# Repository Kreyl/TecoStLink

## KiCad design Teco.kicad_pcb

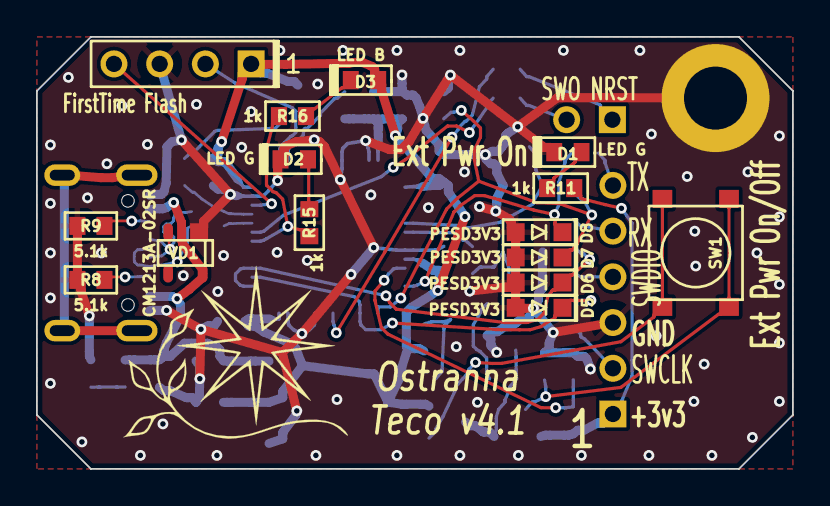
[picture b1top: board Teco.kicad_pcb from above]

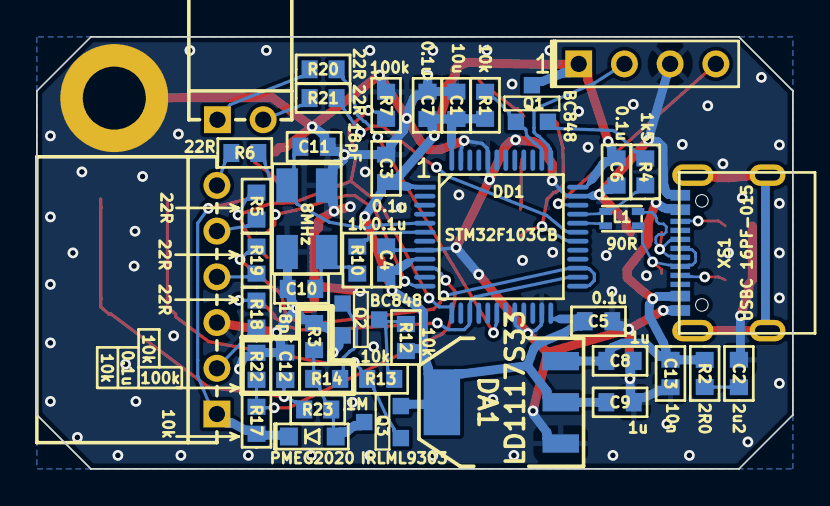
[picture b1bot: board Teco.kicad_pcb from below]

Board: 2 copper layers, 42.0 x 24.0 mm, 59 parts (42 on the bottom side), 40 nets.

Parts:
C1: 10u; CAP_0603
C2: 2u2; CAP_0603
C3, C4, C5, C6, C7, C12: 0.1u; CAP_0603
C8, C9: 1u; CAP_0603
C10, C11: 18pF; CAP_0603
C13: 10n; CAP_0603
D1, D2: LED G; LED_0603
D3: LED B; LED_0603
D4: PMEG2020; SOD323
D5, D6, D7, D8: PESD3V3; SOD323
DA1: LD1117S33; SOT223
DD1: STM32F103CB; LQFP48
HOLE5: HOLE_METALLED; Hole3_5_out6mm
L1: 90R; DLW21SN
Logo1: Logo; Ostranna_12d7_10d1
Q1, Q2: BC848; SOT23-3
Q3: IRLML9303; SOT23-3
R1, R3, R12, R13, R17, R22: 10k; RES_0603
R2: 2R0; RES_0603
R4: 1k5; RES_0603
R5, R6, R18, R19, R20, R21: 22R; RES_0603
R7, R14: 100k; RES_0603
R8, R9: 5.1k; RES0603
R10, R11, R15, R16: 1k; RES_0603
R23: 1M; RES_0603
SW1: BUTTON; BTN_4x4_SMD
VD1: CM1213A−02SR; SOT143
XL2: CONN_4; PLS-4
XL3: CONN_6; PBS-6R-MIRR
XL4: CONN_2; PBS-2R-MIRR
XS1: USBC 16PF-015; USB-C_16pin_16PF-015
XTAL1: 8MHz; 0503x4-4

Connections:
+3v3: C1.1, C3.1, C4.1, C5.1, C6.1, C7.1, C9.1, D3.A, DA1.2 (OUT), DA1.PAD (OUT), DD1.1 (VBAT), DD1.9 (VDDA), DD1.24 (VDD1), DD1.36 (VDD2), DD1.48 (VDD3), Q1.3 (C), Q3.2 (S), R1.2, R12.1, XL2.1
+5v: C8.1, C13.1, DA1.3 (IN), R2.1, VD1.4 (VDD), XS1.A4B9, XS1.B4A9
/AIN1: DD1.10 (ADC1-0/WKUP/PA0), R17.2, R22.1
/EXTPWR: D4.C, R11.2, R17.1, XL3.1
/LED_STLINK: DD1.30 (T1C2/TX1/PA9), R15.2, R16.2
/RXD: D7.C, DD1.13 (ADC1-3/T2C4/T15C2/RX2/PA3), R5.2, R7.1
/STM_JTCK: DD1.37 (SWCLK/JTCK/PA14), XL2.2 (PM)
/STM_JTMS: DD1.34 (SWDIO/JTMS/PA13), XL2.4
/TXD: D8.C, DD1.12 (ADC1-2/T2C3/T15C1/TX2/PA2), R6.2
/T_JTCK: D5.C, DD1.15 (ADC1-5/DAC2/SCK1/PA5), DD1.26 (PB13/SCK2/T1C1N), R18.2
/T_JTMS: D6.C, DD1.25 (PB12/CK3), DD1.27 (PB14/MISO2/T1C2N/(T15C1)), R19.2
/T_NRST: DD1.18 (PB0/T3C3/ADC1-8), R20.2
/T_SWO: DD1.31 (T1C3/RX1/PA10), R21.2
/USB_CC1: R8.2, XS1.A5
/USB_CC2: R9.2, XS1.B5
/USB_D+: DD1.33 (USBDP/PA12), L1.3, R4.1
/USB_D-: DD1.32 (T1C4/USBDM/PA11), L1.2
/USB_DIN+: L1.4, VD1.3 (CH2), XS1.A6, XS1.B6
/USB_DIN-: L1.1, VD1.2 (CH1), XS1.A7, XS1.B7
/USB_RENUM: DD1.38 (JTDI/PA15), Q1.1 (B), R1.1
GND: C1.2, C2.2, C3.2, C4.2, C5.2, C6.2, C7.2, C8.2, C9.2, C10.2, C11.2, C12.2, C13.2, D1.C, D2.C, D5.A, D6.A, D7.A, D8.A, DA1.1 (GND), DD1.8 (VSSA), DD1.20 (PB2/BOOT1), DD1.23 (VSS1), DD1.35 (VSS2), DD1.44 (BOOT0), DD1.47 (VSS3), HOLE5.H, Q2.2 (E), R3.2, R7.2, R8.1, R9.1, R22.2, VD1.1 (GND), XL2.3, XL3.3, XS1.A1B12, XS1.B1A12, XTAL1.H
unnamed: C2.1, R2.2
unnamed: C10.1, R10.1, XTAL1.1
unnamed: C12.1, R23.2, SW1.2
unnamed: D1.A, R11.1
unnamed: D2.A, R15.1
unnamed: D3.C, R16.1
unnamed: C11.1, DD1.5 (OSCIN/(PD0)), XTAL1.2
unnamed: DD1.6 (OSCOUT/(PD1)), R10.2
unnamed: Q1.2 (E), R4.2
unnamed: Q2.1 (B), R14.2
unnamed: Q2.3 (C), R12.2, R13.2
unnamed: D4.A, Q3.3 (D), R3.1, R14.1, R23.1
unnamed: Q3.1 (G), R13.1, SW1.1
unnamed: R5.1, XL3.5
unnamed: R6.1, XL3.6
unnamed: R18.1, XL3.2
unnamed: R19.1, XL3.4
unnamed: R20.1, XL4.1
unnamed: R21.1, XL4.2 (PM)

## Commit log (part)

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2017-04-27 + Sch done, PCB started
2017-04-27 Sch updated Layout done
2017-04-28 Sent to production
2017-05-05 + botloader binaries
2017-05-12 + R to discharge pwr line
2019-04-22 + v3 Sent to factory
2019-04-22 + V2
2019-04-22 v3.1: + Pull-up on RX + legend
2019-11-25 + complete fw
2019-11-25 + STLink upgrade tool v3.7.0. Newer ones do not allow to upgrade it from scratch.
2020-05-28 + Readme + St-Link upgrade
2020-05-29 + Teco v4 + USB renum returned!
2023-10-02 + BlackMagicProbe full firmware
2023-11-03 Add fw binaries
2023-12-01 + First try to construct BMP FW
2023-12-04 Putting files together
2023-12-06 Compiled, seen by host
2023-12-06 It works
2023-12-08 - morse
2023-12-14 - SPI Flash removed
2023-12-14 + rtt
2023-12-15 Refactor Remove #if RTT_ENABLED: make it always enabled
2023-12-22 + How to RTT instruction added
2024-03-25 Download & UsbSerial work ok
2024-03-26 + Implement Pwr Btn * Minor Clean-up RC
2024-09-17 Power control left on button only
2024-09-17 GD32f405 supprt added
2024-10-12 GD32F405 detection improved UART disconnected when DUT powered off by btn
2024-11-13 switch to KiCAD 7
2024-11-13 + 3D case
2024-11-13 PCB thickness 1.6mm
2024-11-14 button rename
2024-11-14 USB-C connector installed, ESD USB protection added, new BOM created
2024-11-14 upgrade complete
2024-12-10 Cyclyc switch: UartON PwrON -> UartOFF PwrOFF -> UartON PwrOff
2025-11-19 + indicate uart on when powering on
2026-03-19 + GD32F470 works
2026-03-29 +gd32f470 added
